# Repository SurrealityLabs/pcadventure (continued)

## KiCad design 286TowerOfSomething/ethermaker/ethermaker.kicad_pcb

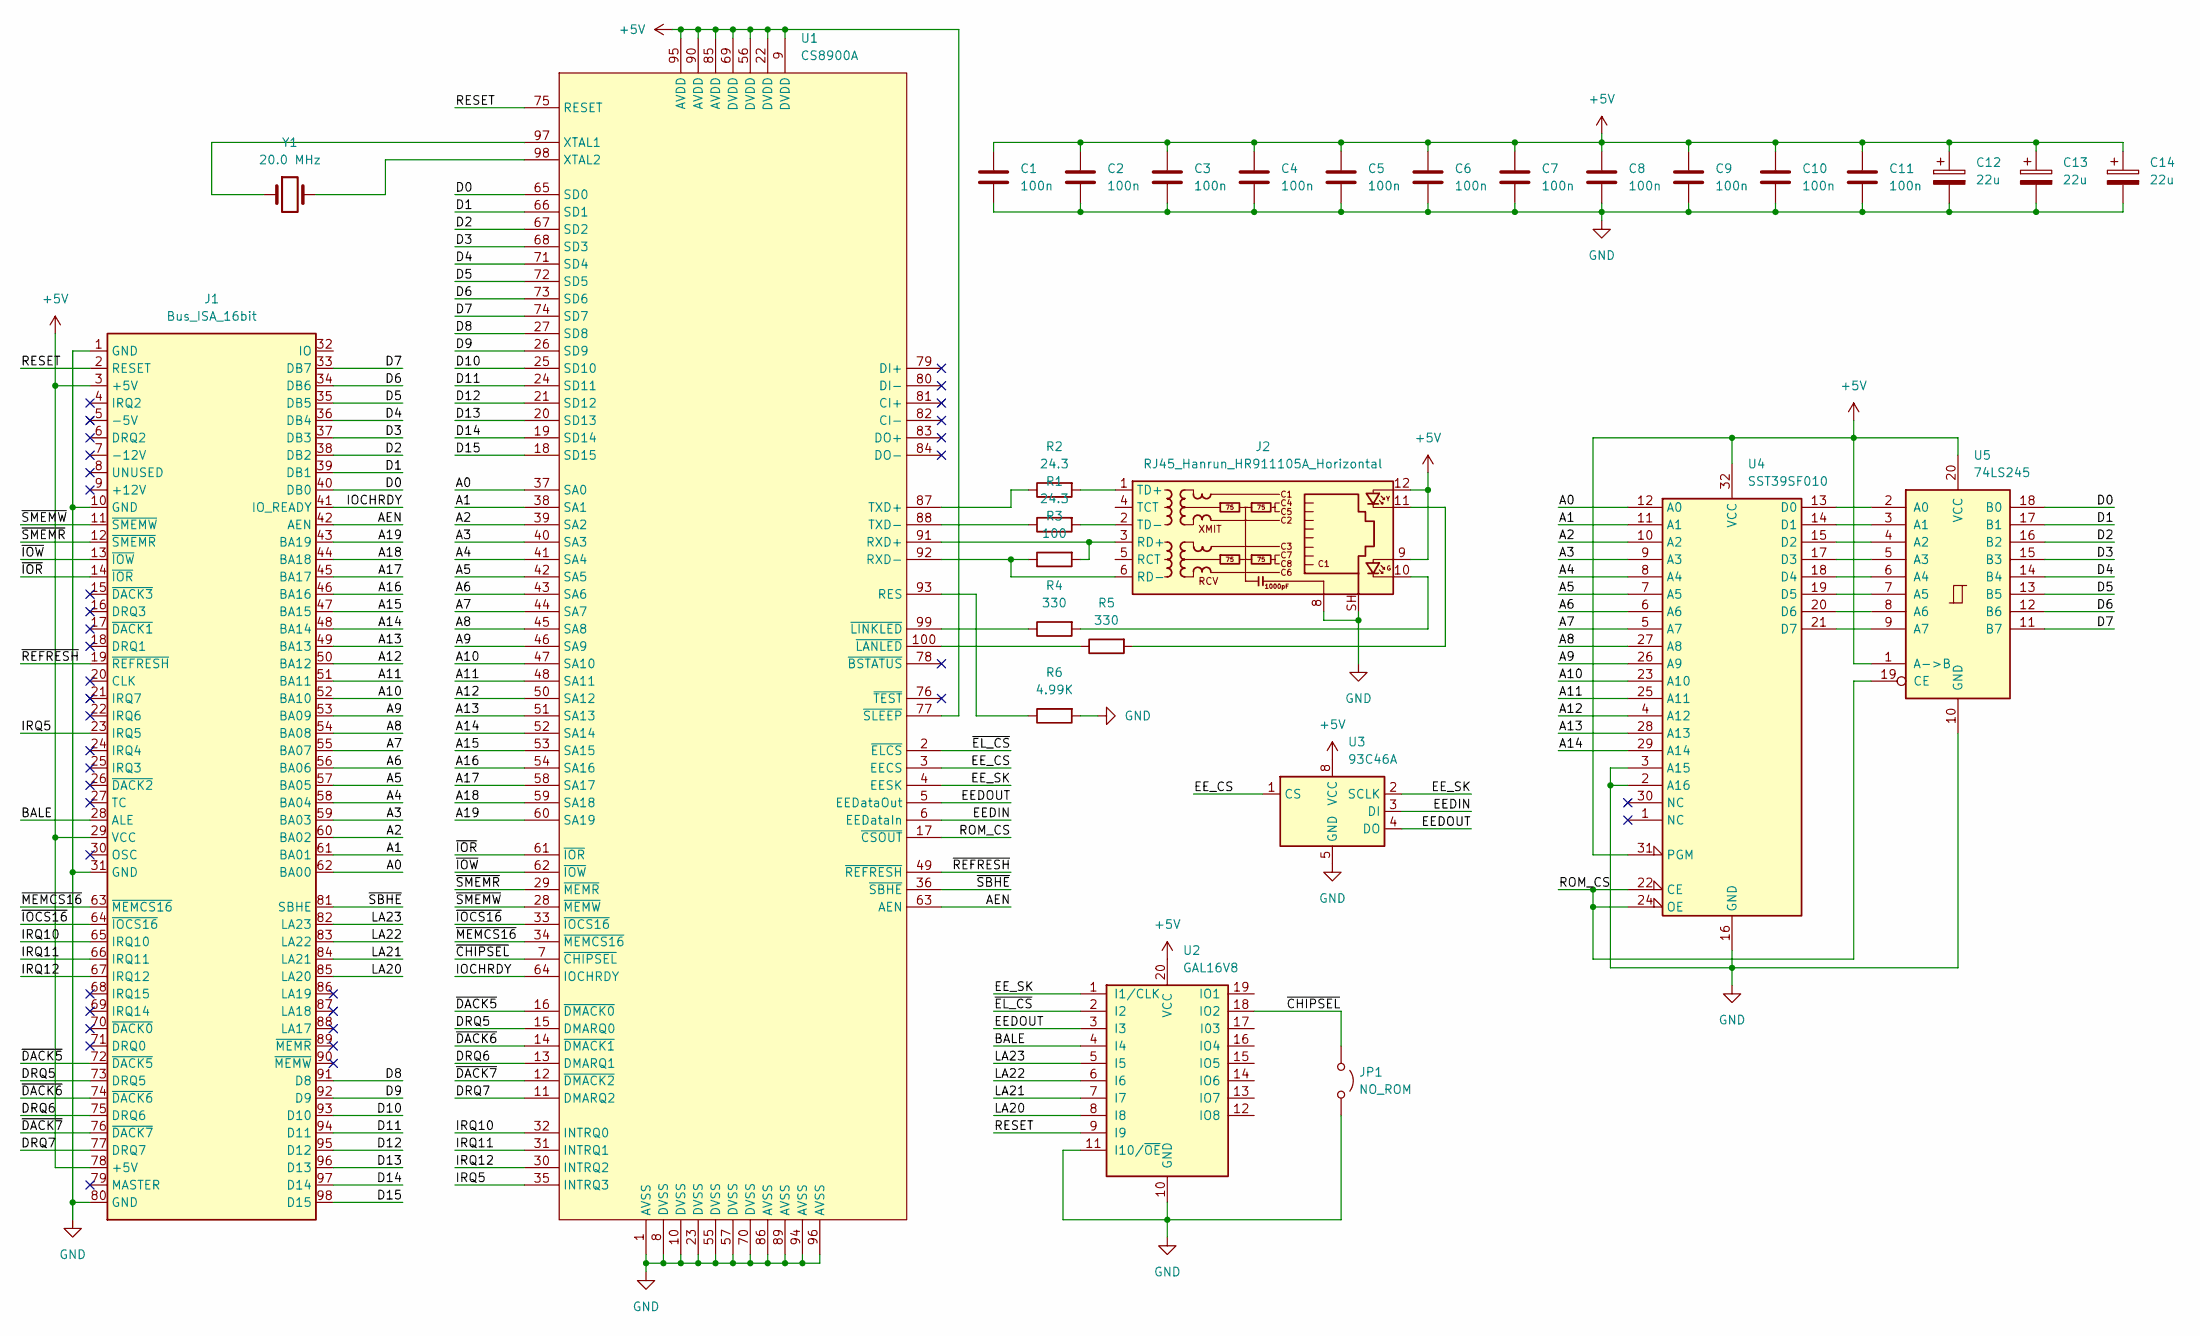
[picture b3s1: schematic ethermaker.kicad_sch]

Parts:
C1, C2, C3, C4, C5, C6, C7, C8, C9, C10, C11: 100n; C_0603_1608Metric_Pad1.08x0.95mm_HandSolder
C12, C13, C14: 22u; CP_Elec_5x5.3
J1: Bus_ISA_16bit; BUS_AT
J2: RJ45_Hanrun_HR911105A_Horizontal
JP1: NO_ROM; SolderJumper-2_P1.3mm_Open_RoundedPad1.0x1.5mm
R1, R2: 24.3; R_0603_1608Metric_Pad0.98x0.95mm_HandSolder
R3: 100; R_0603_1608Metric_Pad0.98x0.95mm_HandSolder
R4, R5: 330; R_0603_1608Metric_Pad0.98x0.95mm_HandSolder
R6: 4.99K; R_0603_1608Metric_Pad0.98x0.95mm_HandSolder
U1: CS8900A; LQFP-100_14x14mm_P0.5mm
U2: GAL16V8; DIP-20_W7.62mm
U3: 93C46A; DIP-8_W7.62mm
U4: SST39SF010; DIP-32_W15.24mm
U5: 74LS245; DIP-20_W7.62mm
Y1: 20.0 MHz; Crystal_HC49-4H_Vertical

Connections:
+5V: C1.1, C2.1, C3.1, C4.1, C5.1, C6.1, C7.1, C8.1, C9.1, C10.1, C11.1, C12.1, C13.1, C14.1, J1.3 (+5V), J1.29 (VCC), J1.78 (+5V), J2.9, J2.12, U1.9 (DVDD), U1.22 (DVDD), U1.56 (DVDD), U1.69 (DVDD), U1.77 (~SLEEP), U1.85 (AVDD), U1.90 (AVDD), U1.95 (AVDD), U2.20 (VCC), U3.8 (VCC), U4.31 (PGM), U4.32 (VCC), U5.1 (A->B), U5.20 (VCC)
/A0: J1.62 (BA00), U1.37 (SA0), U4.12 (A0)
/A1: J1.61 (BA01), U1.38 (SA1), U4.11 (A1)
/A2: J1.60 (BA02), U1.39 (SA2), U4.10 (A2)
/A3: J1.59 (BA03), U1.40 (SA3), U4.9 (A3)
/A4: J1.58 (BA04), U1.41 (SA4), U4.8 (A4)
/A5: J1.57 (BA05), U1.42 (SA5), U4.7 (A5)
/A6: J1.56 (BA06), U1.43 (SA6), U4.6 (A6)
/A7: J1.55 (BA07), U1.44 (SA7), U4.5 (A7)
/A8: J1.54 (BA08), U1.45 (SA8), U4.27 (A8)
/A9: J1.53 (BA09), U1.46 (SA9), U4.26 (A9)
/A10: J1.52 (BA10), U1.47 (SA10), U4.23 (A10)
/A11: J1.51 (BA11), U1.48 (SA11), U4.25 (A11)
/A12: J1.50 (BA12), U1.50 (SA12), U4.4 (A12)
/A13: J1.49 (BA13), U1.51 (SA13), U4.28 (A13)
/A14: J1.48 (BA14), U1.52 (SA14), U4.29 (A14)
/A15: J1.47 (BA15), U1.53 (SA15)
/A16: J1.46 (BA16), U1.54 (SA16)
/A17: J1.45 (BA17), U1.58 (SA17)
/A18: J1.44 (BA18), U1.59 (SA18)
/A19: J1.43 (BA19), U1.60 (SA19)
/AEN: J1.42 (AEN), U1.63 (AEN)
/BALE: J1.28 (ALE), U2.4 (I4)
/D0: J1.40 (DB0), U1.65 (SD0), U5.18 (B0)
/D1: J1.39 (DB1), U1.66 (SD1), U5.17 (B1)
/D2: J1.38 (DB2), U1.67 (SD2), U5.16 (B2)
/D3: J1.37 (DB3), U1.68 (SD3), U5.15 (B3)
/D4: J1.36 (DB4), U1.71 (SD4), U5.14 (B4)
/D5: J1.35 (DB5), U1.72 (SD5), U5.13 (B5)
/D6: J1.34 (DB6), U1.73 (SD6), U5.12 (B6)
/D7: J1.33 (DB7), U1.74 (SD7), U5.11 (B7)
/D8: J1.91 (D8), U1.27 (SD8)
/D9: J1.92 (D9), U1.26 (SD9)
/D10: J1.93 (D10), U1.25 (SD10)
/D11: J1.94 (D11), U1.24 (SD11)
/D12: J1.95 (D12), U1.21 (SD12)
/D13: J1.96 (D13), U1.20 (SD13)
/D14: J1.97 (D14), U1.19 (SD14)
/D15: J1.98 (D15), U1.18 (SD15)
/DRQ5: J1.73 (DRQ5), U1.15 (DMARQ0)
/DRQ6: J1.75 (DRQ6), U1.13 (DMARQ1)
/DRQ7: J1.77 (DRQ7), U1.11 (DMARQ2)
/EEDIN: U1.6 (EEDataIn), U3.3 (DI)
/EEDOUT: U1.5 (EEDataOut), U2.3 (I3), U3.4 (DO)
/EE_CS: U1.3 (EECS), U3.1 (CS)
/EE_SK: U1.4 (EESK), U2.1 (I1/CLK), U3.2 (SCLK)
/IOCHRDY: J1.41 (IO_READY), U1.64 (IOCHRDY)
/IRQ5: J1.23 (IRQ5), U1.35 (INTRQ3)
/IRQ10: J1.65 (IRQ10), U1.32 (INTRQ0)
/IRQ11: J1.66 (IRQ11), U1.31 (INTRQ1)
/IRQ12: J1.67 (IRQ12), U1.30 (INTRQ2)
/LA20: J1.85 (LA20), U2.8 (I8)
/LA21: J1.84 (LA21), U2.7 (I7)
/LA22: J1.83 (LA22), U2.6 (I6)
/LA23: J1.82 (LA23), U2.5 (I5)
/RESET: J1.2 (RESET), U1.75 (RESET), U2.9 (I9)
/ROM_CS: U1.17 (~CSOUT), U4.22 (CE), U4.24 (OE), U5.19 (CE)
/~CHIPSEL: JP1.1 (A), U1.7 (~CHIPSEL), U2.18 (IO2)
/~DACK5: J1.72 (~DACK5), U1.16 (~DMACK0)
/~DACK6: J1.74 (~DACK6), U1.14 (~DMACK1)
/~DACK7: J1.76 (~DACK7), U1.12 (~DMACK2)
/~EL_CS: U1.2 (~ELCS), U2.2 (I2)
/~IOCS16: J1.64 (~IOCS16), U1.33 (~IOCS16)
/~IOR: J1.14 (~IOR), U1.61 (~IOR)
/~IOW: J1.13 (~IOW), U1.62 (~IOW)
/~MEMCS16: J1.63 (~MEMCS16), U1.34 (~MEMCS16)
/~REFRESH: J1.19 (~REFRESH), U1.49 (~REFRESH)
/~SBHE: J1.81 (SBHE), U1.36 (~SBHE)
/~SMEMR: J1.12 (~SMEMR), U1.29 (~MEMR)
/~SMEMW: J1.11 (~SMEMW), U1.28 (~MEMW)
GND: C1.2, C2.2, C3.2, C4.2, C5.2, C6.2, C7.2, C8.2, C9.2, C10.2, C11.2, C12.2, C13.2, C14.2, J1.1 (GND), J1.10 (GND), J1.31 (GND), J1.80 (GND), J2.8, J2.SH, JP1.2 (B), R6.2, U1.1 (AVSS), U1.8 (DVSS), U1.10 (DVSS), U1.23 (DVSS), U1.55 (DVSS), U1.57 (DVSS), U1.70 (DVSS), U1.86 (AVSS), U1.89 (AVSS), U1.94 (AVSS), U1.96 (AVSS), U2.10 (GND), U2.11 (I10/~OE), U3.5 (GND), U4.2 (A16), U4.3 (A15), U4.16 (GND), U5.10 (GND)
unnamed: J2.10, R4.2
unnamed: J2.11, R5.2
unnamed: J2.3 (RD+), R3.2, U1.91 (RXD+)
unnamed: J2.6 (RD-), R3.1, U1.92 (RXD-)
unnamed: J2.1 (TD+), R2.2
unnamed: J2.2 (TD-), R1.2
unnamed: R6.1, U1.93 (RES)
unnamed: R2.1, U1.87 (TXD+)
unnamed: R1.1, U1.88 (TXD-)
unnamed: U1.97 (XTAL1), Y1.1
unnamed: U1.98 (XTAL2), Y1.2
unnamed: R5.1, U1.100 (~LANLED)
unnamed: R4.1, U1.99 (~LINKLED)
unnamed: U4.13 (D0), U5.2 (A0)
unnamed: U4.14 (D1), U5.3 (A1)
unnamed: U4.15 (D2), U5.4 (A2)
unnamed: U4.17 (D3), U5.5 (A3)
unnamed: U4.18 (D4), U5.6 (A4)
unnamed: U4.19 (D5), U5.7 (A5)
unnamed: U4.20 (D6), U5.8 (A6)
unnamed: U4.21 (D7), U5.9 (A7)

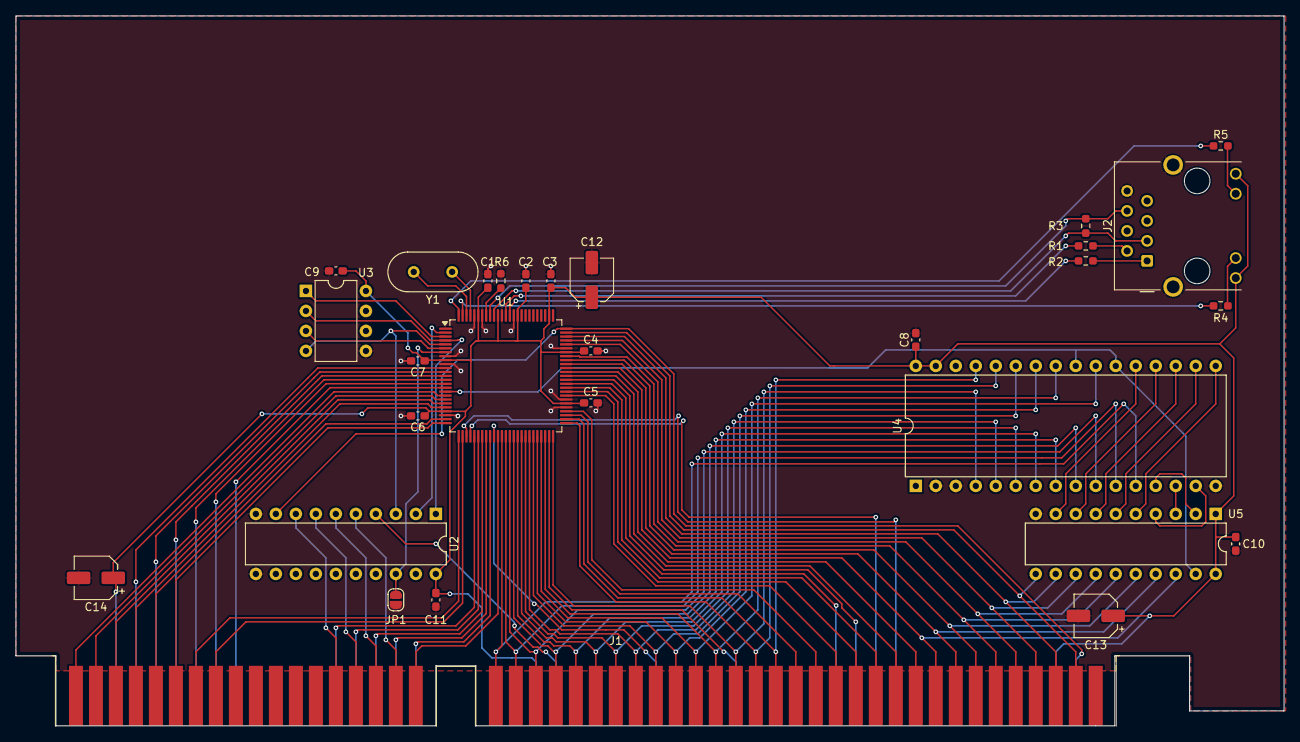
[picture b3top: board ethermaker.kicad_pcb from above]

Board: 2 copper layers, 161.1 x 90.2 mm, 29 parts (0 on the bottom side), 92 nets.

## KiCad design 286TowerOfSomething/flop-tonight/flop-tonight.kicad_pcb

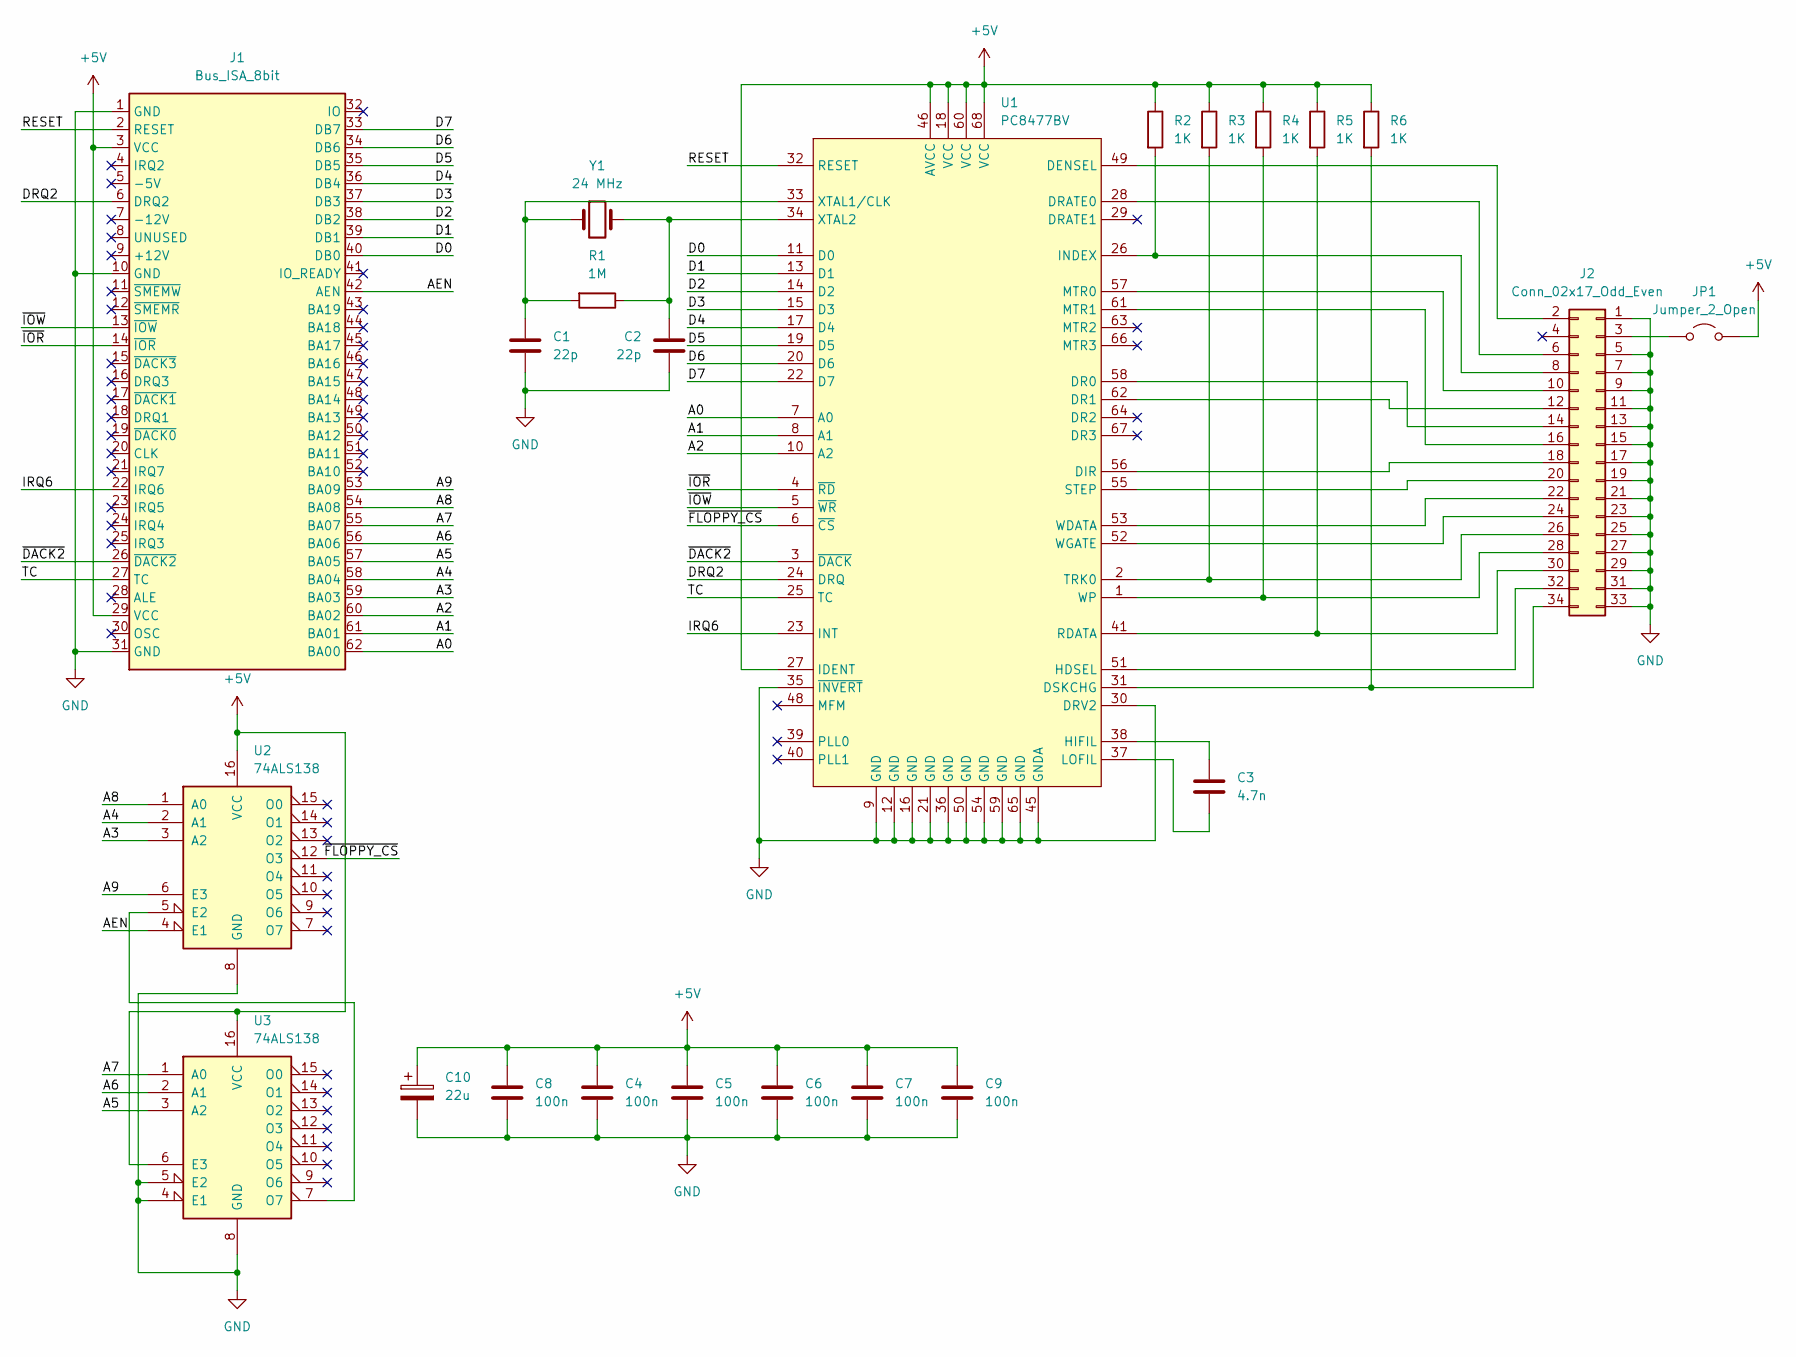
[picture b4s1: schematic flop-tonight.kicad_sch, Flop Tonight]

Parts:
C1, C2: 22p; C_0603_1608Metric_Pad1.08x0.95mm_HandSolder
C3: 4.7n; C_0603_1608Metric_Pad1.08x0.95mm_HandSolder
C4, C5, C6, C7, C8, C9: 100n; C_0603_1608Metric_Pad1.08x0.95mm_HandSolder
C10: 22u; CP_Elec_5x5.3
J1: Bus_ISA_8bit; BUS_AT_8BIT
J2: Conn_02x17_Odd_Even; IDC-Header_2x17_P2.54mm_Vertical
JP1: Jumper_2_Open; PinHeader_1x02_P2.54mm_Vertical
R1: 1M; R_0603_1608Metric_Pad0.98x0.95mm_HandSolder
R2, R3, R4, R5, R6: 1K; R_0603_1608Metric_Pad0.98x0.95mm_HandSolder
U1: PC8477BV; PLCC-68_THT-Socket
U2, U3: 74ALS138; DIP-16_W7.62mm
Y1: 24 MHz; Crystal_HC49-U_Vertical

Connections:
+5V: C4.1, C5.1, C6.1, C7.1, C8.1, C9.1, C10.1, J1.3 (VCC), J1.29 (VCC), JP1.2 (B), R2.1, R3.1, R4.1, R5.1, R6.1, U1.18 (VCC), U1.27 (IDENT), U1.46 (AVCC), U1.60 (VCC), U1.68 (VCC), U2.16 (VCC), U3.6 (E3), U3.16 (VCC)
/A0: J1.62 (BA00), U1.7 (A0)
/A1: J1.61 (BA01), U1.8 (A1)
/A2: J1.60 (BA02), U1.10 (A2)
/A3: J1.59 (BA03), U2.3 (A2)
/A4: J1.58 (BA04), U2.2 (A1)
/A5: J1.57 (BA05), U3.3 (A2)
/A6: J1.56 (BA06), U3.2 (A1)
/A7: J1.55 (BA07), U3.1 (A0)
/A8: J1.54 (BA08), U2.1 (A0)
/A9: J1.53 (BA09), U2.6 (E3)
/AEN: J1.42 (AEN), U2.4 (E1)
/D0: J1.40 (DB0), U1.11 (D0)
/D1: J1.39 (DB1), U1.13 (D1)
/D2: J1.38 (DB2), U1.14 (D2)
/D3: J1.37 (DB3), U1.15 (D3)
/D4: J1.36 (DB4), U1.17 (D4)
/D5: J1.35 (DB5), U1.19 (D5)
/D6: J1.34 (DB6), U1.20 (D6)
/D7: J1.33 (DB7), U1.22 (D7)
/DRQ2: J1.6 (DRQ2), U1.24 (DRQ)
/IRQ6: J1.22 (IRQ6), U1.23 (INT)
/RESET: J1.2 (RESET), U1.32 (RESET)
/TC: J1.27 (TC), U1.25 (TC)
/~DACK2: J1.26 (~DACK2), U1.3 (~DACK)
/~FLOPPY_CS: U1.6 (~CS), U2.12 (O3)
/~IOR: J1.14 (~IOR), U1.4 (~RD)
/~IOW: J1.13 (~IOW), U1.5 (~WR)
GND: C1.2, C2.2, C4.2, C5.2, C6.2, C7.2, C8.2, C9.2, C10.2, J1.1 (GND), J1.10 (GND), J1.31 (GND), J2.1, J2.5, J2.7, J2.9, J2.11, J2.13, J2.15, J2.17, J2.19, J2.21, J2.23, J2.25, J2.27, J2.29, J2.31, J2.33, U1.9 (GND), U1.12 (GND), U1.16 (GND), U1.21 (GND), U1.30 (DRV2), U1.35 (~INVERT), U1.36 (GND), U1.45 (GNDA), U1.50 (GND), U1.54 (GND), U1.59 (GND), U1.65 (GND), U2.8 (GND), U3.4 (E1), U3.5 (E2), U3.8 (GND)
unnamed: J2.2, U1.49 (DENSEL)
unnamed: J2.3, JP1.1 (A)
unnamed: J2.6, U1.28 (DRATE0)
unnamed: J2.8, R2.2, U1.26 (INDEX)
unnamed: J2.10, U1.57 (MTR0)
unnamed: J2.12, U1.62 (DR1)
unnamed: J2.14, U1.58 (DR0)
unnamed: J2.16, U1.61 (MTR1)
unnamed: J2.18, U1.56 (DIR)
unnamed: J2.20, U1.55 (STEP)
unnamed: J2.22, U1.53 (WDATA)
unnamed: J2.24, U1.52 (WGATE)
unnamed: J2.26, R3.2, U1.2 (TRK0)
unnamed: J2.28, R4.2, U1.1 (WP)
unnamed: J2.30, R5.2, U1.41 (RDATA)
unnamed: J2.32, U1.51 (HDSEL)
unnamed: J2.34, R6.2, U1.31 (DSKCHG)
unnamed: C3.1, U1.38 (HIFIL)
unnamed: C3.2, U1.37 (LOFIL)
unnamed: C1.1, R1.2, U1.33 (XTAL1/CLK), Y1.1
unnamed: C2.1, R1.1, U1.34 (XTAL2), Y1.2
unnamed: U2.5 (E2), U3.7 (O7)

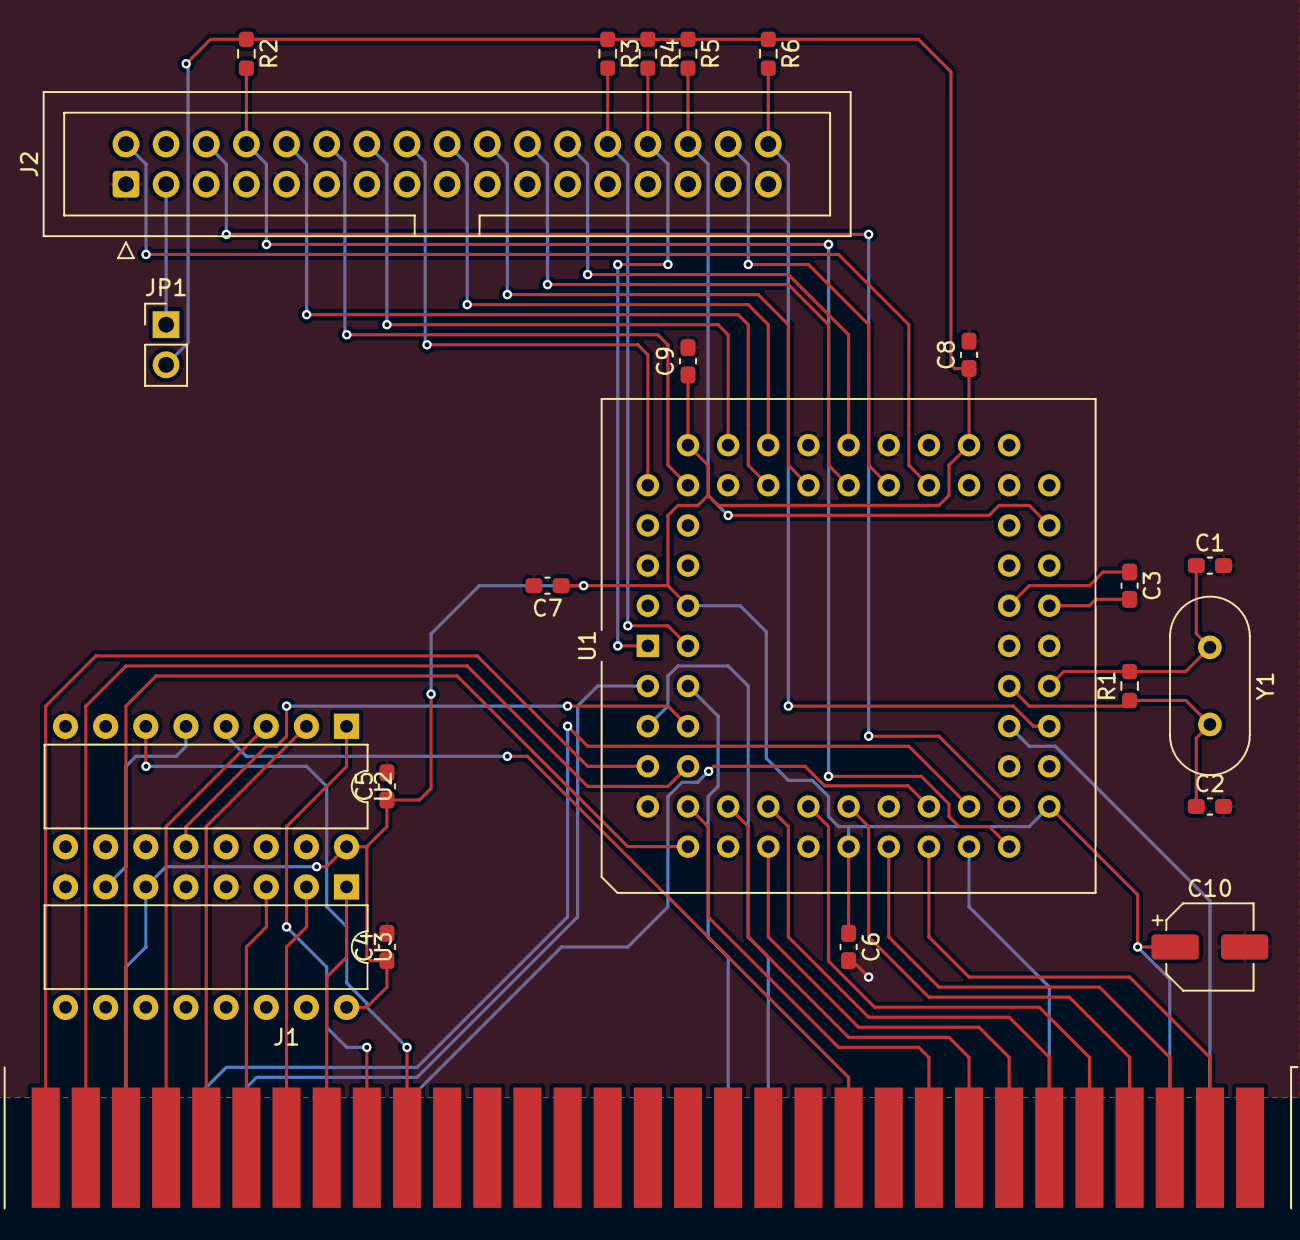
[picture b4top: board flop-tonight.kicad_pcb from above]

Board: 2 copper layers, 23 parts (0 on the bottom side), 51 nets.

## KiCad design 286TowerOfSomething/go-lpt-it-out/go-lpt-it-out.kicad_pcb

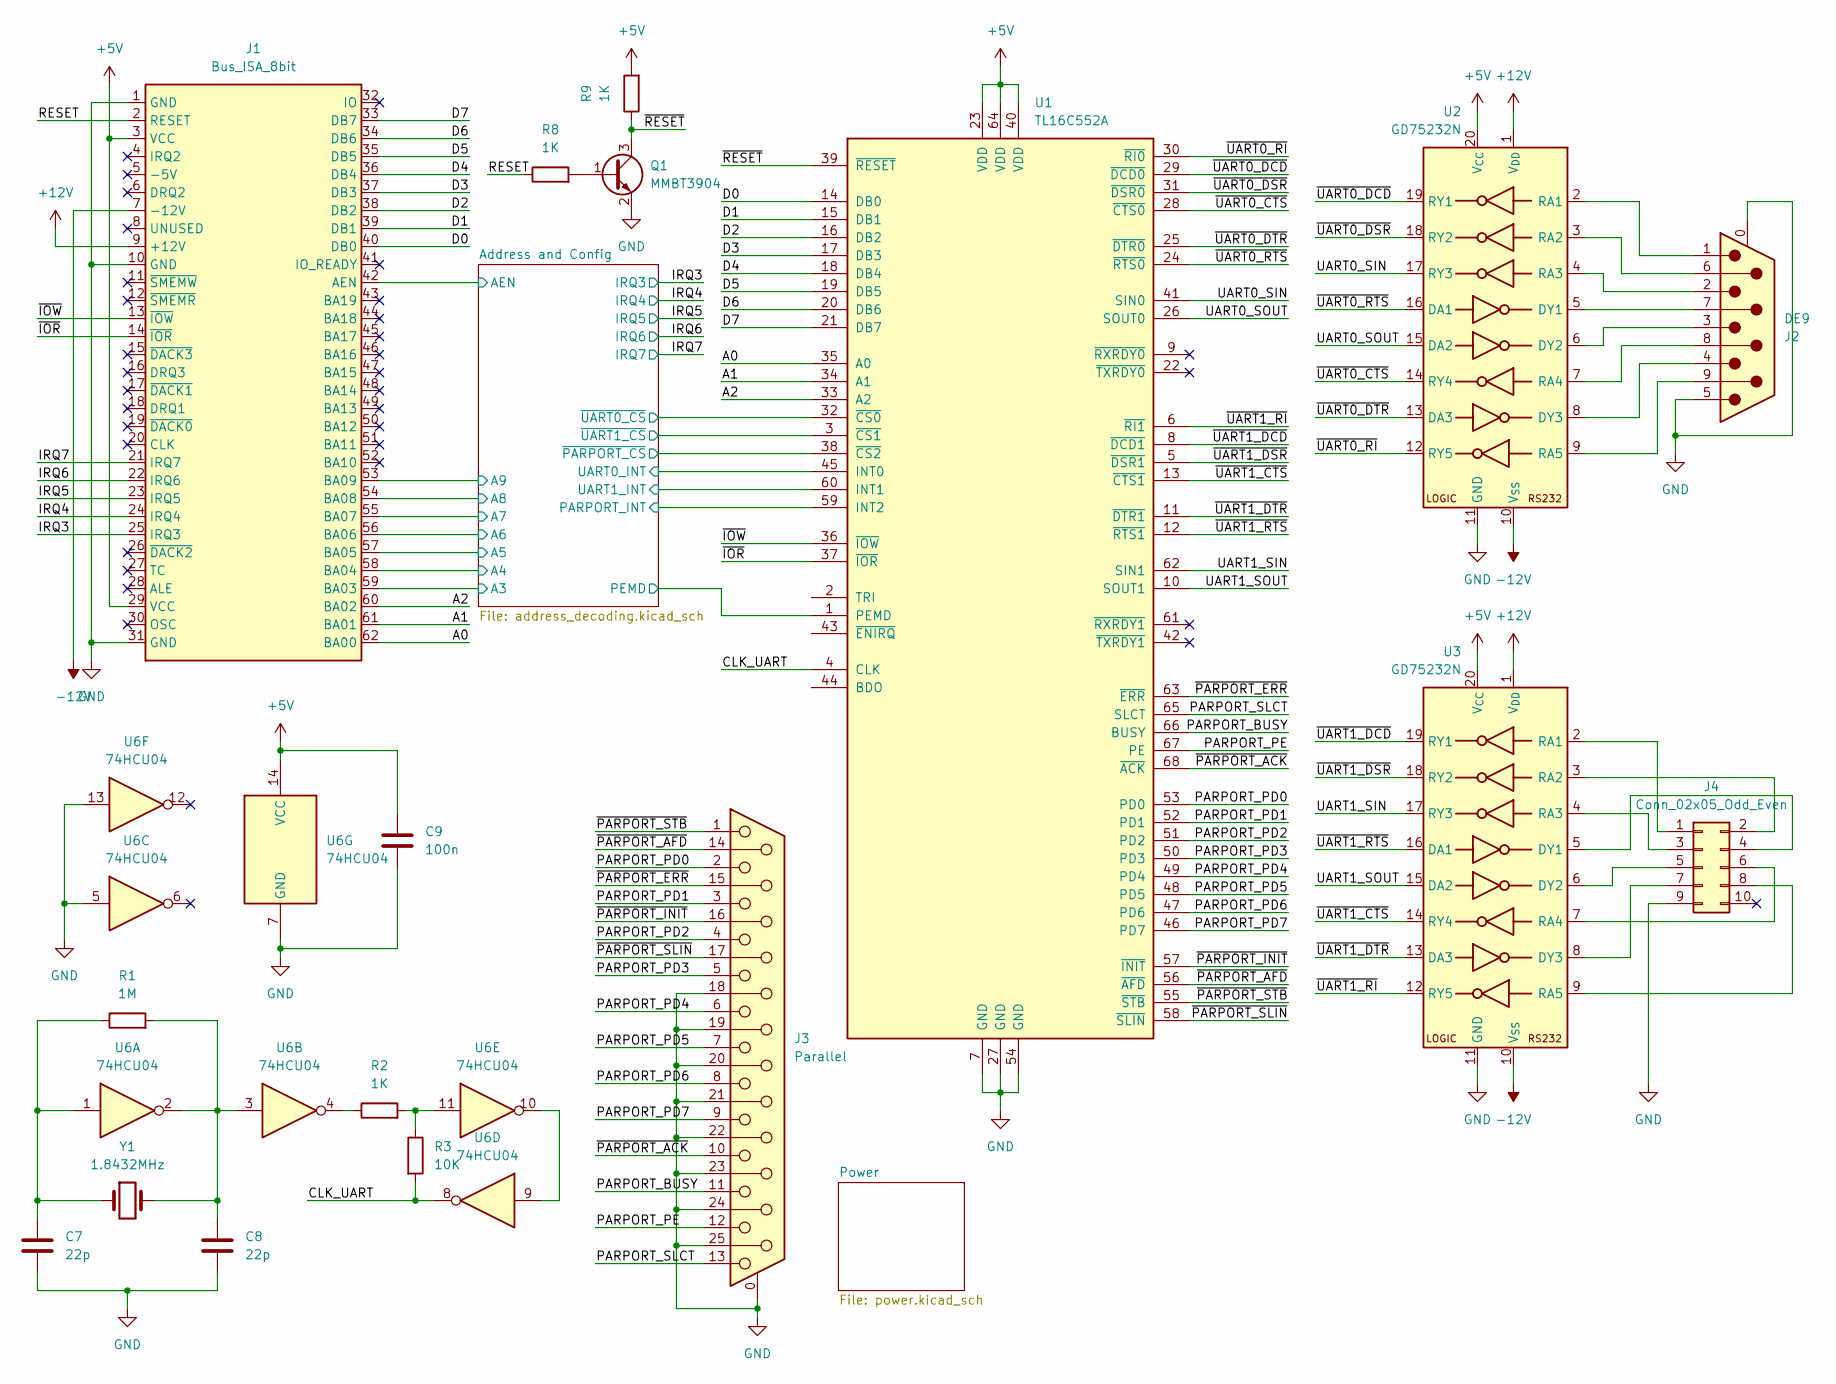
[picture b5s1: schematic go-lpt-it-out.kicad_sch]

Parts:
C7, C8: 22p; C_0603_1608Metric_Pad1.08x0.95mm_HandSolder
C9: 100n; C_0603_1608Metric_Pad1.08x0.95mm_HandSolder
J1: Bus_ISA_8bit; BUS_AT_8BIT
J2: DE9; DSUB-9_Male_Horizontal_P2.77x2.84mm_EdgePinOffset7.70mm_Hou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
J3: Parallel; DSUB-25_Female_Horizontal_P2.77x2.84mm_EdgePinOffset7.70mm_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
J4: Conn_02x05_Odd_Even; IDC-Header_2x05_P2.54mm_Vertical
Q1: MMBT3904; SOT-23
R1: 1M; R_0603_1608Metric_Pad0.98x0.95mm_HandSolder
R2, R8, R9: 1K; R_0603_1608Metric_Pad0.98x0.95mm_HandSolder
R3: 10K; R_0603_1608Metric_Pad0.98x0.95mm_HandSolder
U1: TL16C552A; PLCC-68_THT-Socket
U2, U3: GD75232N; DIP-20_W7.62mm
U6: 74HCU04; SO-14_3.9x8.65mm_P1.27mm
Y1: 1.8432MHz; Crystal_HC49-U_Vertical

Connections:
+5V: C9.1, J1.3 (VCC), J1.29 (VCC), R9.2, U1.23 (VDD), U1.40 (VDD), U1.64 (VDD), U2.20 (V_{CC}), U3.20 (V_{CC}), U6.14 (VCC); also elsewhere on the board
+12V: J1.9 (+12V), U2.1 (V_{DD}), U3.1 (V_{DD}); also elsewhere on the board
-12V: J1.7 (-12V), U2.10 (V_{SS}), U3.10 (V_{SS}); also elsewhere on the board
/A0: J1.62 (BA00), U1.35 (A0)
/A1: J1.61 (BA01), U1.34 (A1)
/A2: J1.60 (BA02), U1.33 (A2)
/Address and Config/A3: J1.59 (BA03); also elsewhere on the board
/Address and Config/A4: J1.58 (BA04); also elsewhere on the board
/Address and Config/A5: J1.57 (BA05); also elsewhere on the board
/Address and Config/A6: J1.56 (BA06); also elsewhere on the board
/Address and Config/A7: J1.55 (BA07); also elsewhere on the board
/Address and Config/A8: J1.54 (BA08); also elsewhere on the board
/Address and Config/A9: J1.53 (BA09); also elsewhere on the board
/Address and Config/AEN: J1.42 (AEN); also elsewhere on the board
/Address and Config/PARPORT_INT: U1.59 (INT2); also elsewhere on the board
/Address and Config/PEMD: U1.1 (PEMD); also elsewhere on the board
/Address and Config/UART0_INT: U1.45 (INT0); also elsewhere on the board
/Address and Config/UART1_INT: U1.60 (INT1); also elsewhere on the board
/Address and Config/~PARPORT_CS: U1.38 (~CS2); also elsewhere on the board
/Address and Config/~UART0_CS: U1.32 (~CS0); also elsewhere on the board
/Address and Config/~UART1_CS: U1.3 (~CS1); also elsewhere on the board
/CLK_UART: R3.2, U1.4 (CLK), U6.8
/D0: J1.40 (DB0), U1.14 (DB0)
/D1: J1.39 (DB1), U1.15 (DB1)
/D2: J1.38 (DB2), U1.16 (DB2)
/D3: J1.37 (DB3), U1.17 (DB3)
/D4: J1.36 (DB4), U1.18 (DB4)
/D5: J1.35 (DB5), U1.19 (DB5)
/D6: J1.34 (DB6), U1.20 (DB6)
/D7: J1.33 (DB7), U1.21 (DB7)
/IRQ3: J1.25 (IRQ3); also elsewhere on the board
/IRQ4: J1.24 (IRQ4); also elsewhere on the board
/IRQ5: J1.23 (IRQ5); also elsewhere on the board
/IRQ6: J1.22 (IRQ6); also elsewhere on the board
/IRQ7: J1.21 (IRQ7); also elsewhere on the board
/PARPORT_BUSY: J3.11, U1.66 (BUSY)
/PARPORT_PD0: J3.2, U1.53 (PD0)
/PARPORT_PD1: J3.3, U1.52 (PD1)
/PARPORT_PD2: J3.4, U1.51 (PD2)
/PARPORT_PD3: J3.5, U1.50 (PD3)
/PARPORT_PD4: J3.6, U1.49 (PD4)
/PARPORT_PD5: J3.7, U1.48 (PD5)
/PARPORT_PD6: J3.8, U1.47 (PD6)
/PARPORT_PD7: J3.9, U1.46 (PD7)
/PARPORT_PE: J3.12, U1.67 (PE)
/PARPORT_SLCT: J3.13, U1.65 (SLCT)
/RESET: J1.2 (RESET), R8.1
/UART0_SIN: U1.41 (SIN0), U2.17 (RY3)
/UART0_SOUT: U1.26 (SOUT0), U2.15 (DA2)
/UART1_SIN: U1.62 (SIN1), U3.17 (RY3)
/UART1_SOUT: U1.10 (SOUT1), U3.15 (DA2)
/~IOR: J1.14 (~IOR), U1.37 (~IOR)
/~IOW: J1.13 (~IOW), U1.36 (~IOW)
/~PARPORT_ACK: J3.10, U1.68 (~ACK)
/~PARPORT_AFD: J3.14, U1.56 (~AFD)
/~PARPORT_ERR: J3.15, U1.63 (~ERR)
/~PARPORT_INIT: J3.16, U1.57 (~INIT)
/~PARPORT_SLIN: J3.17, U1.58 (~SLIN)
/~PARPORT_STB: J3.1, U1.55 (~STB)
/~RESET: Q1.3 (C), R9.1, U1.39 (~RESET)
/~UART0_CTS: U1.28 (~CTS0), U2.14 (RY4)
/~UART0_DCD: U1.29 (~DCD0), U2.19 (RY1)
/~UART0_DSR: U1.31 (~DSR0), U2.18 (RY2)
/~UART0_DTR: U1.25 (~DTR0), U2.13 (DA3)
/~UART0_RI: U1.30 (~RI0), U2.12 (RY5)
/~UART0_RTS: U1.24 (~RTS0), U2.16 (DA1)
/~UART1_CTS: U1.13 (~CTS1), U3.14 (RY4)
/~UART1_DCD: U1.8 (~DCD1), U3.19 (RY1)
/~UART1_DSR: U1.5 (~DSR1), U3.18 (RY2)
/~UART1_DTR: U1.11 (~DTR1), U3.13 (DA3)
/~UART1_RI: U1.6 (~RI1), U3.12 (RY5)
/~UART1_RTS: U1.12 (~RTS1), U3.16 (DA1)
GND: C7.2, C8.2, C9.2, J1.1 (GND), J1.10 (GND), J1.31 (GND), J2.0 (PAD), J2.5, J3.0 (PAD), J3.18, J3.19, J3.20, J3.21, J3.22, J3.23, J3.24, J3.25, J4.9, Q1.2 (E), U1.7 (GND), U1.27 (GND), U1.54 (GND), U2.11 (GND), U3.11 (GND), U6.5, U6.7 (GND), U6.13; also elsewhere on the board
unnamed: C7.1, R1.1, U6.1, Y1.1
unnamed: C8.1, R1.2, U6.2, U6.3, Y1.2
unnamed: J4.1, U3.2 (RA1)
unnamed: J4.2, U3.3 (RA2)
unnamed: J4.3, U3.4 (RA3)
unnamed: J4.4, U3.5 (DY1)
unnamed: J4.5, U3.6 (DY2)
unnamed: J4.6, U3.7 (RA4)
unnamed: J4.7, U3.8 (DY3)
unnamed: J4.8, U3.9 (RA5)
unnamed: Q1.1 (B), R8.2
unnamed: R2.1, U6.4
unnamed: R2.2, R3.1, U6.11
unnamed: J2.7, U2.5 (DY1)
unnamed: J2.3, U2.6 (DY2)
unnamed: J2.4, U2.8 (DY3)
unnamed: J2.1, U2.2 (RA1)
unnamed: J2.6, U2.3 (RA2)
unnamed: J2.2, U2.4 (RA3)
unnamed: J2.8, U2.7 (RA4)
unnamed: J2.9, U2.9 (RA5)
unnamed: U6.9, U6.10

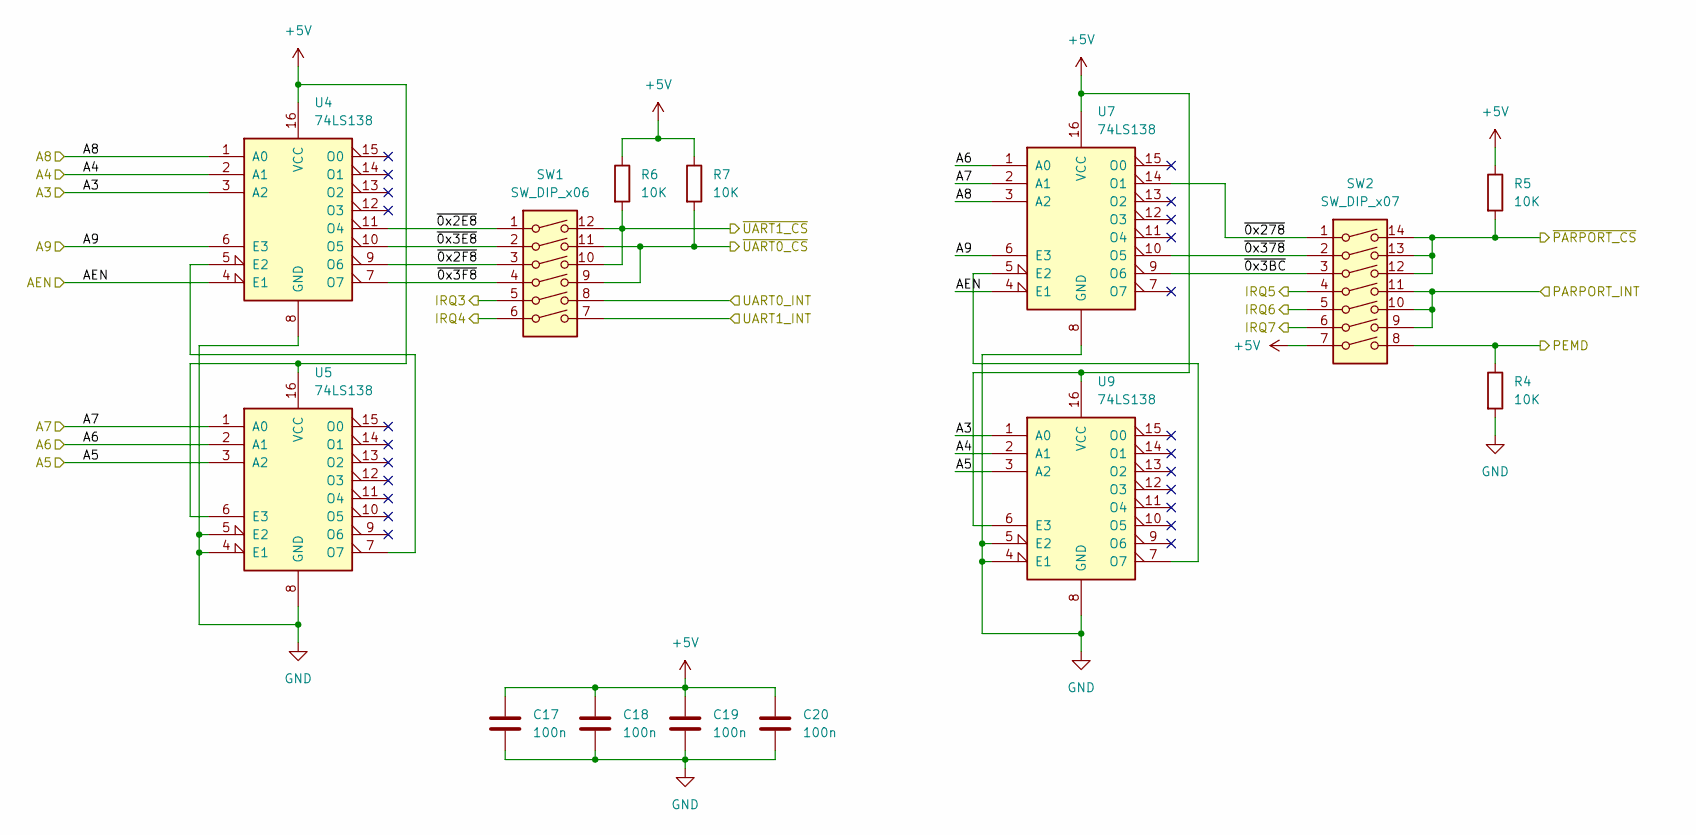
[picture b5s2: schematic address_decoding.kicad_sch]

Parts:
C17, C18, C19, C20: 100n; C_0603_1608Metric_Pad1.08x0.95mm_HandSolder
R4, R5, R6, R7: 10K
SW1: SW_DIP_x06
SW2: SW_DIP_x07
U4, U5, U7, U9: 74LS138; DIP-16_W7.62mm

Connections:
+5V: C17.1, C18.1, C19.1, C20.1, R5.1, R6.1, R7.1, SW2.7, U4.16 (VCC), U5.6 (E3), U5.16 (VCC), U7.16 (VCC), U9.6 (E3), U9.16 (VCC); also elsewhere on the board
/Address and Config/A3: U4.3 (A2), U9.1 (A0); also elsewhere on the board
/Address and Config/A4: U4.2 (A1), U9.2 (A1); also elsewhere on the board
/Address and Config/A5: U5.3 (A2), U9.3 (A2); also elsewhere on the board
/Address and Config/A6: U5.2 (A1), U7.1 (A0); also elsewhere on the board
/Address and Config/A7: U5.1 (A0), U7.2 (A1); also elsewhere on the board
/Address and Config/A8: U4.1 (A0), U7.3 (A2); also elsewhere on the board
/Address and Config/A9: U4.6 (E3), U7.6 (E3); also elsewhere on the board
/Address and Config/AEN: U4.4 (E1), U7.4 (E1); also elsewhere on the board
/Address and Config/PARPORT_INT: SW2.9, SW2.10, SW2.11; also elsewhere on the board
/Address and Config/PEMD: R4.1, SW2.8; also elsewhere on the board
/Address and Config/UART0_INT: SW1.8; also elsewhere on the board
/Address and Config/UART1_INT: SW1.7; also elsewhere on the board
/Address and Config/~0x2E8: SW1.1, U4.11 (O4)
/Address and Config/~0x2F8: SW1.3, U4.9 (O6)
/Address and Config/~0x3BC: SW2.3, U7.9 (O6)
/Address and Config/~0x3E8: SW1.2, U4.10 (O5)
/Address and Config/~0x3F8: SW1.4, U4.7 (O7)
/Address and Config/~0x278: SW2.1, U7.14 (O1)
/Address and Config/~0x378: SW2.2, U7.10 (O5)
/Address and Config/~PARPORT_CS: R5.2, SW2.12, SW2.13, SW2.14; also elsewhere on the board
/Address and Config/~UART0_CS: R7.2, SW1.9, SW1.11; also elsewhere on the board
/Address and Config/~UART1_CS: R6.2, SW1.10, SW1.12; also elsewhere on the board
/IRQ3: SW1.5; also elsewhere on the board
/IRQ4: SW1.6; also elsewhere on the board
/IRQ5: SW2.4; also elsewhere on the board
/IRQ6: SW2.5; also elsewhere on the board
/IRQ7: SW2.6; also elsewhere on the board
GND: C17.2, C18.2, C19.2, C20.2, R4.2, U4.8 (GND), U5.4 (E1), U5.5 (E2), U5.8 (GND), U7.8 (GND), U9.4 (E1), U9.5 (E2), U9.8 (GND); also elsewhere on the board
unnamed: U4.5 (E2), U5.7 (O7)
unnamed: U7.5 (E2), U9.7 (O7)

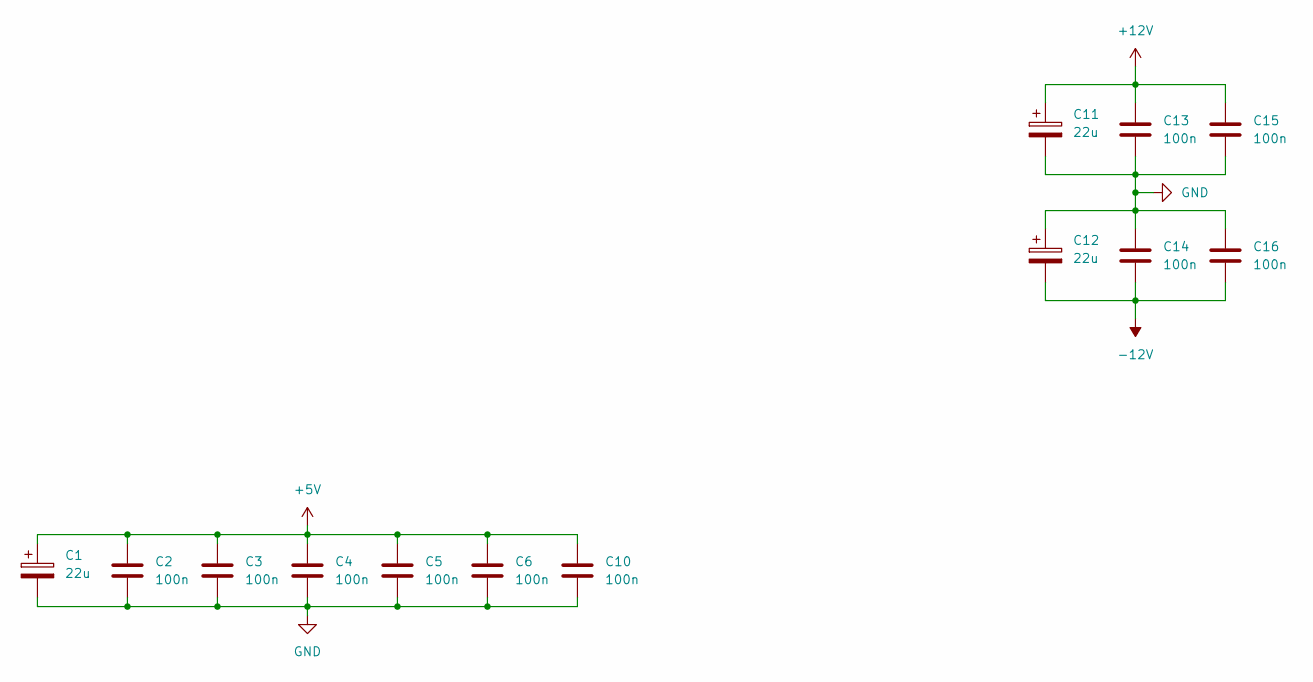
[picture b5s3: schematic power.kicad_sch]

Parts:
C1, C11, C12: 22u; CP_Elec_5x5.3
C2, C3, C4, C5, C6, C10, C13, C14, C15, C16: 100n; C_0603_1608Metric_Pad1.08x0.95mm_HandSolder

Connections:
+5V: C1.1, C2.1, C3.1, C4.1, C5.1, C6.1, C10.1; also elsewhere on the board
+12V: C11.1, C13.1, C15.1; also elsewhere on the board
-12V: C12.2, C14.2, C16.2; also elsewhere on the board
GND: C1.2, C2.2, C3.2, C4.2, C5.2, C6.2, C10.2, C11.2, C12.1, C13.2, C14.1, C15.2, C16.1; also elsewhere on the board
